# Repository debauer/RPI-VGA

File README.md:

# RPI-VGA
VGA Hat for Raspberry Pis

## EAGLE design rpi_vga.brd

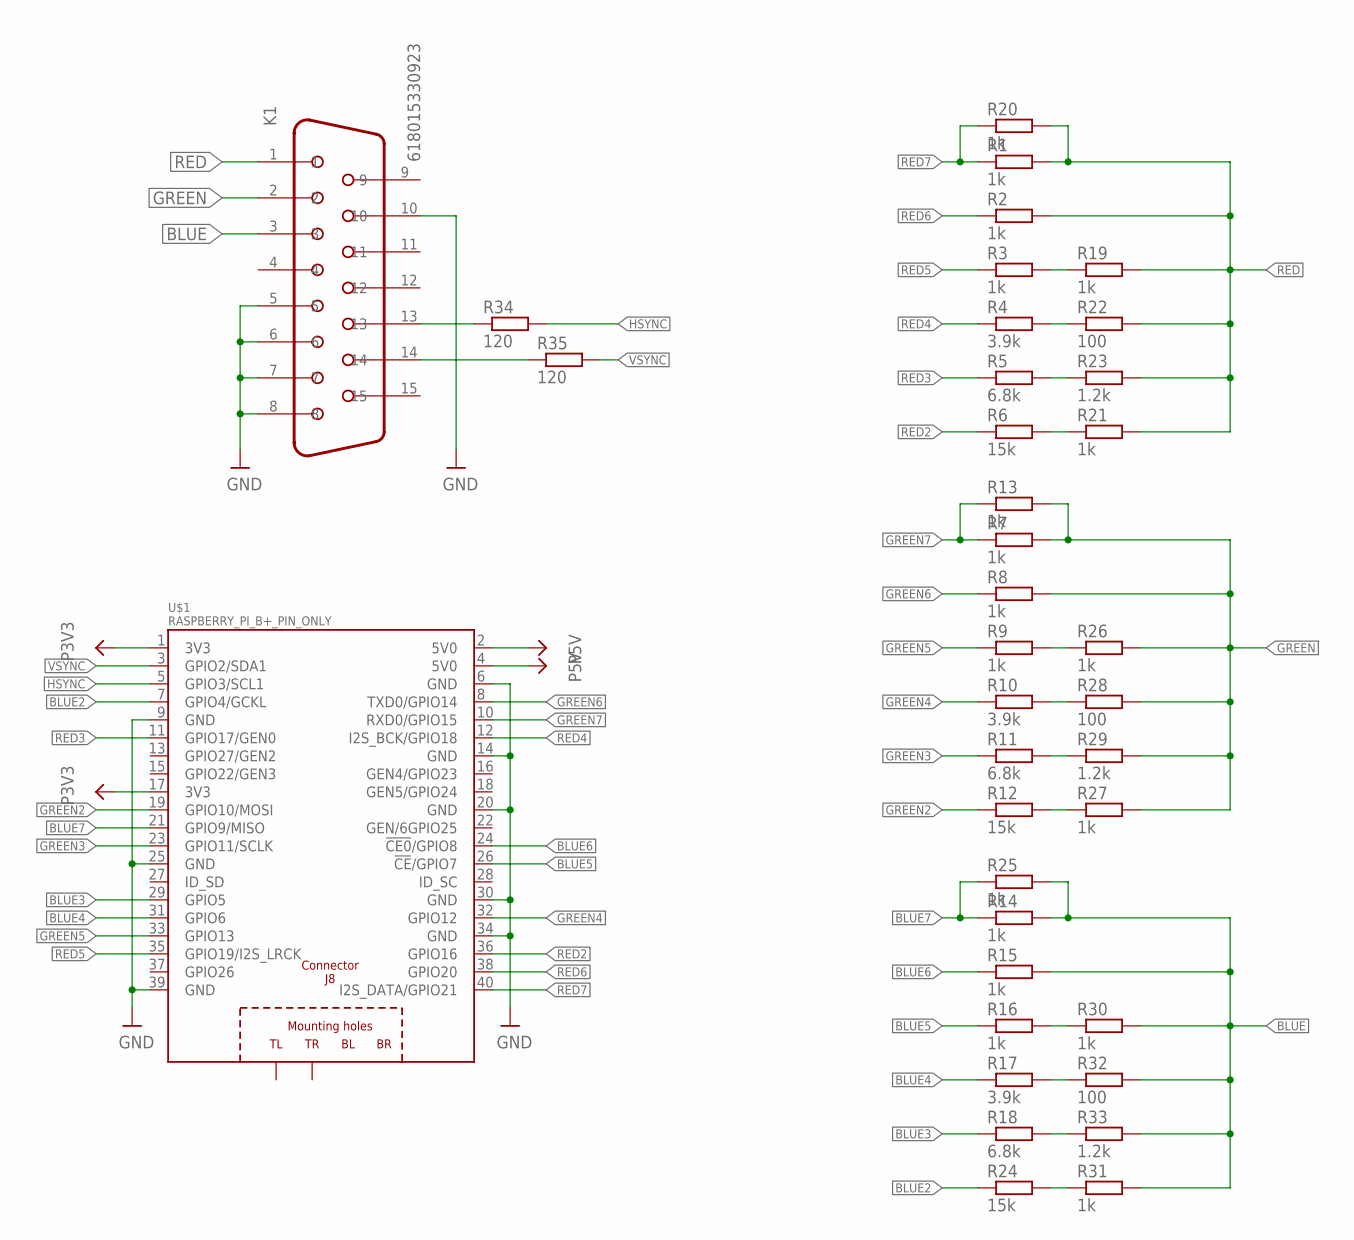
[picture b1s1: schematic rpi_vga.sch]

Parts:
K1: 618015330923
R1, R2, R3, R7, R8, R9, R13, R14, R15, R16, R19, R20, R21, R25, R26, R27, R30, R31: 1k; R0603
R4, R10, R17: 3.9k; R0603
R5, R11, R18: 6.8k; R0603
R6, R12, R24: 15k; R0603
R22, R28, R32: 100; R0603
R23, R29, R33: 1.2k; R0603
R34, R35: 120; R0603
U$1: RASPBERRY_PI_B+_PIN_ONLY

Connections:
BLUE: K1.3, R14.2, R15.2, R25.2, R30.2, R31.2, R32.2, R33.2
BLUE2: R24.1, U$1.7 (GPIO4/GCKL)
BLUE3: R18.1, U$1.29 (GPIO5)
BLUE4: R17.1, U$1.31 (GPIO6)
BLUE5: R16.1, U$1.26 (!CE!/GPIO7)
BLUE6: R15.1, U$1.24 (!CE0!/GPIO8)
BLUE7: R14.1, R25.1, U$1.21 (GPIO9/MISO)
GND: K1.5, K1.6, K1.7, K1.8, K1.10, U$1.6 (GND), U$1.9 (GND), U$1.14 (GND), U$1.20 (GND), U$1.25 (GND), U$1.30 (GND), U$1.34 (GND), U$1.39 (GND)
GREEN: K1.2, R7.2, R8.2, R13.2, R26.2, R27.2, R28.2, R29.2
GREEN2: R12.1, U$1.19 (GPIO10/MOSI)
GREEN3: R11.1, U$1.23 (GPIO11/SCLK)
GREEN4: R10.1, U$1.32 (GPIO12)
GREEN5: R9.1, U$1.33 (GPIO13)
GREEN6: R8.1, U$1.8 (TXD0/GPIO14)
GREEN7: R7.1, R13.1, U$1.10 (RXD0/GPIO15)
HSYNC: R34.2, U$1.5 (GPIO3/SCL1)
unnamed: R3.2, R19.1
unnamed: R6.2, R21.1
unnamed: R4.2, R22.1
unnamed: R5.2, R23.1
unnamed: R12.2, R27.1
unnamed: R11.2, R29.1
unnamed: R10.2, R28.1
unnamed: R9.2, R26.1
unnamed: R24.2, R31.1
unnamed: R18.2, R33.1
unnamed: R17.2, R32.1
unnamed: R16.2, R30.1
unnamed: K1.13, R34.1
unnamed: K1.14, R35.1
P3V3: U$1.1 (3V3), U$1.17 (3V3)
P5V: U$1.2 (5V0), U$1.4 (5V0)
RED: K1.1, R1.2, R2.2, R19.2, R20.2, R21.2, R22.2, R23.2
RED2: R6.1, U$1.36 (GPIO16)
RED3: R5.1, U$1.11 (GPIO17/GEN0)
RED4: R4.1, U$1.12 (I2S_BCK/GPIO18)
RED5: R3.1, U$1.35 (GPIO19/I2S_LRCK)
RED6: R2.1, U$1.38 (GPIO20)
RED7: R1.1, R20.1, U$1.40 (I2S_DATA/GPIO21)
VSYNC: R35.2, U$1.3 (GPIO2/SDA1)

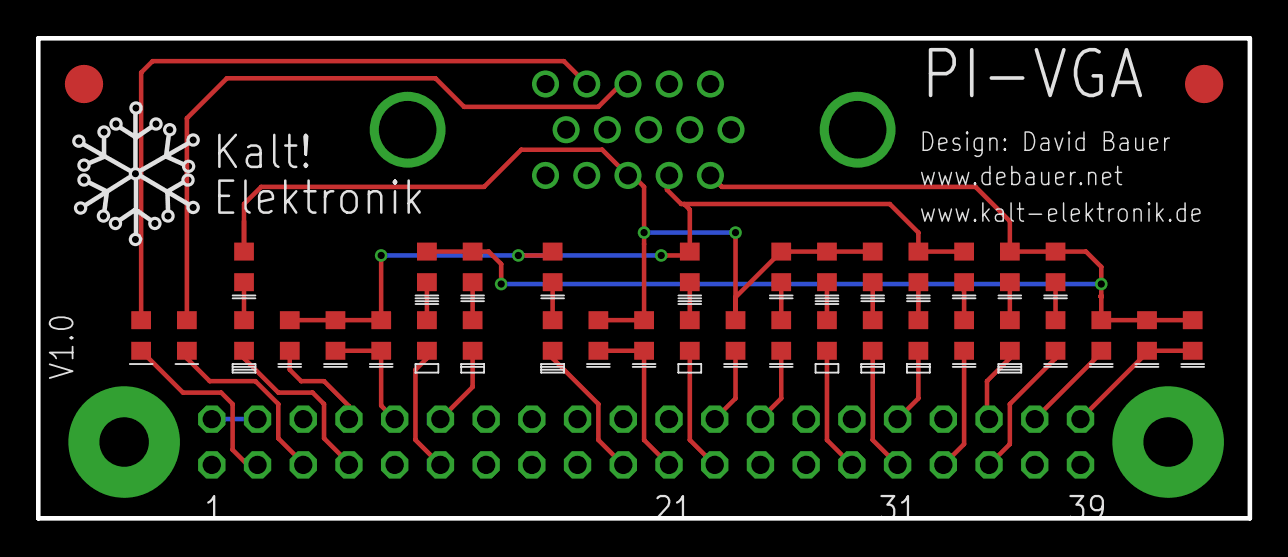
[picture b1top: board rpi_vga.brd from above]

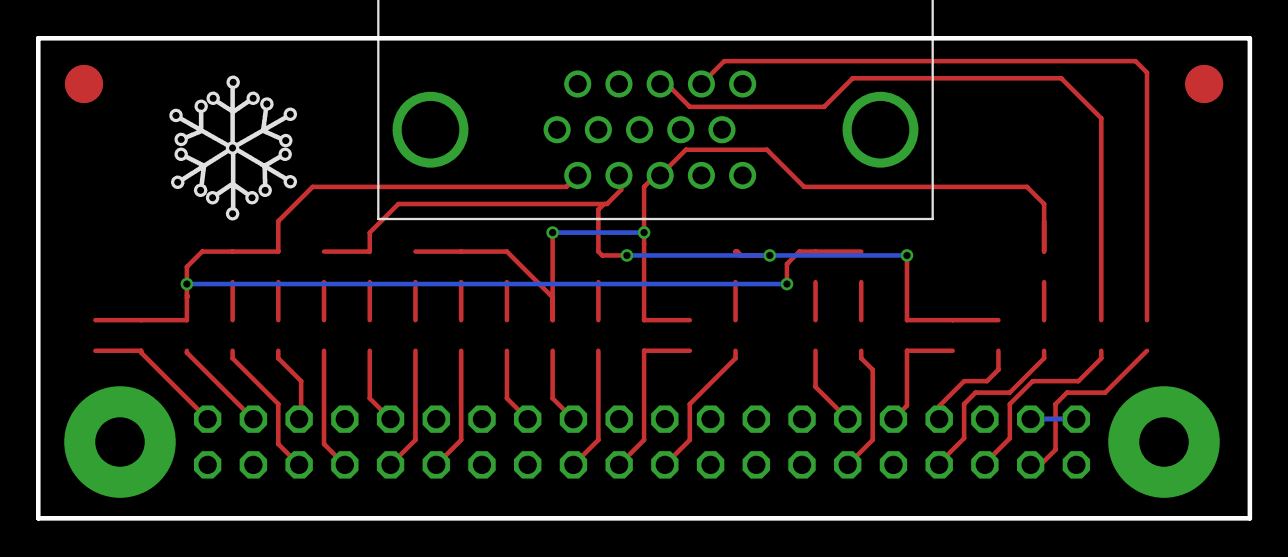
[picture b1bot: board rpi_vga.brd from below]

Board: 2 copper layers, 67.3 x 26.7 mm, 41 parts (2 on the bottom side), 40 nets.

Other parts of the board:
U$2: KALT!ELEKTRONIK
U$3, U$4: PASSMARK
U$5: SNOW

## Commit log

2019-01-29 added untested board

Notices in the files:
parts and their libraries:
Wuerth_Elektronik_eiCan_Communication_Co: Copyright: Würth Elektronik
